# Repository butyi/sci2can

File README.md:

# sci2can

SCI to CAN gateway

## Introduction

This project was developed to receive large data packets from SCI
(RS232 UART without MAX232 line driver) and forward data to CAN
to be available on CAN based tool-chain for analysis purpose.

I decided, this is the perfect moment to get use S08D family, because this
supports faster SCI baud rates than GZ family what I know well.
Therefore I searched my dusty DEMO9S08DZ60 demo board in the deep of cupboard.

## Software

Software is pure assembly code. Funny, it is just 454 bytes long.

### Modules

To understand my description below you may need to look at the related part in
[processor reference manual](https://www.nxp.com/docs/en/data-sheet/MC9S08DZ60.pdf).

#### Central Processor Unit (S08CPUV3)
 
Regarding assembly commands read
[HCS08RMV1.pdf](https://www.nxp.com/docs/en/reference-manual/HCS08RMV1.pdf).
Now (when I am writing this) it is not available on this link even though
I have downloaded from here some weeks before. I have stored it
[here](https://github.com/butyi/sci2can/raw/master/hw/HCS08RMV1.pdf).

My most often read parts are
- Instruction Set Summary (from page 121)
- Branch summary table on sheet of BRA instruction (page 232)

#### Parallel Input/Output Control

To prevent extra current consumption caused by flying not connected input ports,
all ports shall be configured as output. I have configured ports to low level
output by default.
There are only some exceptions for the used ports, where this default
initialization is not proper. For example inputs pins.
This default initialization is proper for FET and OSCILL_SUPP pins, so there is
no specific code for these pins.

#### Multi-purpose Clock Generator (S08MCGV1)

MCG is configured to PEE mode. But this mode can be reached through other modes.
See details in
[AN3499](https://www.nxp.com/docs/en/application-note/AN3499.pdf).
Bus frequency is only 8MHz now, while theoretical maximum is 20MHz.
So here there is improvement potential if software execution is not enough fast.

I have measured bus clock by this code.

Really 8 Mhz, because 8 MHz is 125ns, 10 cycle is 1250ns, which can be seen between edges.

#### Serial Communications Interface (S08SCIV4)

SCI clock is driven by Bus Clock. Maximal baud rate is Bus Clock divided by 16.
Since my Bus Clock is 8MHz, maximum baud rate is 500k baud. Now I just need
baud 125k in this application. It is enough to enable only RX direction.
Data is coming in burst, many bytes immediately after each other. There is
idle period between data bursts.
I use Rx and Idle interrupts. Rx interrupt stores received byte in RAM buffer.
Idle interrupt is invoked when there is one byte long idle state on the serial
line after active period. I use this event to recognize end of data packet
reception. At this moment CAN transmission can be initiated (if packet looks
good) and prepare SCI to next packet.

#### Freescale Controller Area Network (S08MSCANV1)

Regarding CAN clock it is proposed to use external clock directly. With 4MHz
crystal maximum baud rate is 500k baud. This is enough for my needs.
CAN bit consists of 8 time quanta. Sample point is 75% (6+2 tq).
Only transmission is used. Receive related registers are not initialized.
But Tx interrupt is used. Message preparation is done by interrupt routine.
Transmission is triggered by enable Tx interrupt. Then interrupt will send
all CAN messages one after another. Last message disables the interrupt to
stop the transmission of data burst.
Automatic BufOff recovery is configured, there is no other error handling. 
After CAN module initialization, an info message is sent to CAN. This contains
software identification information, like application identifier, software
revision, build date.

### Main loop

#### Structure

Software does not have any operation system. It is not needed, especially
because there no task in main loop. Everything is executed in interrupt
routines.

#### Initialization

Stack, ports, needed modules are initialized one by one.

#### Main activity

The following procedure is executed cyclically.
First SCI Rx interrupt fills up the RAM buffer with data.
After Idle interrupt is called. If amount of received data is proper,
CAN transmission is initialized by enable CAN Tx interrupt.
Then CAN Tx interrupts will send out all data from RAM buffer to CAN.
Last CAN message disables itself (CAN Tx interrupt).
Additional features of hardware is not handled by software yet.

#### Status LED

Meantime RTC interrupt handles the status LED.
The following codes are visible on LED.
- 0001, Short 25% On flash: There is no SCI communication.
- 0011, Medium 50%-50% On-Off flash: Received SCI bytes are not enough.
- 0111, Long 75% On flash: Data cannot be sent to CAN.
- 1111, Always On: Everything are OK, data is forwarded to CAN properly.

#### CAN message structure

The 96 data bytes are transmitted in 12 messages. The CAN ID is the position of
first byte of message in the SCI buffer multiplied by 8. This means
- ID of first message is zero
- ID of second message is 8*8 = 64 dec = 40hex
- ID of third message is 16*8 = 128 dec = 80hex
- ... and so on.

#### Debug support

If OSCILL_SUPP is enabled by compiler switch, execution timing of software
parts can be watched on not used uC pins by oscilloscope.
Here are oscilloscope screenshots about software activity.

- Blue is SCI line. Bursts are visible.

- Blue is SCI Bursts. Red is PTE0 pin, where rising edge is first Rx interrupt
after the idle period, faling edge is idle interrupt.

- Blue is SCI Bursts. Red is PTE1 pin, where rising edge is CAN Tx interrupt
enable, faling edge is end of last CAN Tx interrupt.

- Blue is SCI Bursts. Red is PTE4 pin, high during SCI Rx interrupt execution.

- Blue is SCI Bursts. Red is PTE5 pin, high during CAN Tx interrupt execution.

- Blue is PTE3 pin, high during RTC periodic timer interrupt execution.

- Blue is PTE3 pin, length of RTC periodic timer interrupt execution.

- Blue is PTE4 pin, length of SCI Rx interrupt execution.

- Blue is PTE5 pin, length of CAN Tx interrupt execution.

- Blue is SCI Rx bursts, red is CAN Tx burst.

- Blue is SCI Rx burst, red is SCI Rx interrupt execution.

### Compile

- Download assembler from [aspisys.com](http://www.aspisys.com/asm8.htm).
  It works on both Linux and Windows.
- Check out the repo
- Run my bash file `./c`.
  Or run `asm8 prg.asm` on Linux, `asm8.exe prg.asm` on Windows.
- prg.s19 is now ready to download.

### Download

I have already written [downloader/bootloader for DZ family](https://github.com/butyi/dzbl/).

- First download the bootloader (dzbl/prg.s19) by [USBDM](https://sourceforge.net/projects/usbdm/)
- Create CAN or SCI connection between MCU and PC
- Copy `dzdl.py` to `~/bin/` folder and add executable attribute by `chmox +x ~/bin/dzdl.py`. This is only needed once.
- Run bash file `./p`.

## Hardware

After successful operation of software on demo board I decided to design a
specific PCB.

### Requirements

- At least the following connector pins are needed for gateway function:
  - Ground
  - Power supply ( +7V ... +38V )
  - Serial data input line
  - CAN Low
  - CAN High
- Supply power input must support both 12V and 24V systems.
- Supply power reverse polarity protection needed.
- Small power supply dissipation.
- SCI does not need MAX232 driver because there isn't in the transmitter too.
- SCI port must be protected against connect to supply (+38V).
- CAN transceiver is needed.
- CAN Built in terminator resistor is needed.
- Status LED needed with software control.
- Standard BDM port for software download.
- Small board with direct wire connection (not specific connector).

### Microcontroller

I have used MC9S08DZ60. It is enough for such a small project like this.
Assembler, downloader for both Linux and Windows are available for free for this
family. It costs around 1€.
This is my first application with DZ family controller. After finish the
project, and I have to say, I like it! :) It is really better than GZ family.

Refer to
[processor reference manual](https://www.nxp.com/docs/en/data-sheet/MC9S08DZ60.pdf).

### Clock

External Crystal is used for better CAN performances, this is proposed
by uC manufacturer. Passive parts around are also according to datasheet and
similar to development board circuit.
4MHz is enough up to CAN baud rate 500k when external clock is selected.
For 1Mbaud support I selected rather bus clock of bootloader (16MHz), even though external crystal is proposed.
Crystal is now pin type, since via is need anyway, now the pins holes are vias.

### Connector

I used what I have at home. It is two 3 pins screw connector for wires. 

The connector is not necessary to be mounted, wires can be soldered directly
into the holes. It saves some money and height.

### Power supply

Power input starts with Ds1 diode for reverse polarity protection.
Same circuit as 7805 replacement was designed on the main board.
Search "7805 replacement switching regulator" on Internet.
It uses ME3116. 1A output, max input voltage is 40V.
I just recognized, transient suppression diode is needed on the input. 
Without this protection the supply could damaged at 24V due sparks during 
switch on. I have choosen SMAJ33A.
There is electrolit capacitor on input voltage.
There are also some filter capacitors on uC supply. 
Once is very close to the microcontroller.

### BDM port

BDM port is like proposed in datasheet. This matches to USBDM developer
interface which I use. Single pin communication line (BKGD) has external pull
up resistor, even if it is not necessary.
Reset pin has simple external pull up resistor and filter capacitor.
This port is only needded for software update.
The connector contains extra pins. Details are below.

### SCI input

SCI input is connected to RX pin of SCI2 module. There are serial resistors
for protection against its connection to 24V.
Next is Ui1 74HC1G125GW as impedance adapter. This provides much higher impedance
input than uC pin.
There is Di2 BZT52C4V7 transient suppressor diode to save further parts of
circuit against high voltage tranzients. 
Especially because PTE port has no built in clamp diode to supply.

When Ui1 is mounted, Ri3 and Ri4 are not needed.
Ri3 and Ri4 are designed when pin is used for normal digit or analogue input. 

Ui1 provides perfect shape and amplitude signal for uC input pin.
Here is a screenshot about shape of SCI signal on the uC pin (RxD1).

### CAN output

CAN uses PCA82C251 transceiver. Since there will be point-point connection
on this CAN and other side usually does not have terminator resistor,
there is built in CAN line terminator resistor (Rc2) with 100 Ohm.
Why not 120ohm? Good question.
To limit number of different parts, I have tried to use 100ohm, 1k, 10k, 100k,
1M resistors and 10nF, 100nF, 1uF, 10uF capacitors as many places as possible.
I could buy these parts by 1€/5000pcs. To store it, the cheapest solution
is to buy empty creme holder box in the pharmacy. :smile:
Turning back to CAN.
CAN hardware supports high baud rates up to 1MBaud, but does not support CANFD. 

### Status LED

Status LED (D3) is connected to PTD2. Level high on pin will switch on the LED.
LED is controlled by the software.

Status LED and power LED are near to each other on the back of PCB
intentionally. Plastic box have a hole where the LEDs are, and PCB is fixed in
the box by glue gun. This glue is usually enough transparent to be LED light
visible outside while it is still dust resistant.

### Additional features

Board was designed to be usable for other purposes as well, as much as the
board size allows it. Therefore some components and solutions were also
added to hardware. These are not needed for the original function,
but I hope these will be useful for other functions in the future with the same
board. These components are marked by * on the schematic. These are not need to
be mounted for simple gateway function.

#### Inputs

SCI input is also connected to PTA0. It allows to be used as analogue input.
In this case Ri4 was designed to be used as low side of a voltage divider.
If filter is needed, filter capacitor can be soldered on the top of Ri4 or the
zener.
Similar circuit is also available on the other IO pin without pull down resisor.
When IO pins is used as output, input circuit can be used to monitor the output.

#### Outputs

Hardware has two low side FET outputs. These can switch some external loads,
like lamp, buzzer, relay, or similar.
Gate is pulled down to close FET while port is not yet controlled.
FET was intentionally connected to timer output pins, because this makes outputs
pulse and PWM capable.

OUT ports can also be used as timer input if FET is not mounted but instead a
suitable resistor is mounted between source and gate pins of FET. In this case
this resistor together with gate pull down resistor are a voltage divider.
Filter capacitor (if needed) can be soldered on the top of pull down resistor.
Since FETs are connected to timer ports, this way timer can be used for
pulse length measurement, frequency measurement or similar.

#### Supply measurement

Since there was enough place on PCB and remained several not used ports,
voltage divider was designed from power supply input (UZ) and connected to
PTA5 analogue measurement capable port. With this parts supply voltage can
be measured by the software and used for any purpose.

#### BDM extra pins

The original 6 pins connector contains also SCI1 Rx and Tx pins.
This is designed to be used for software update and debug terminal.

I have extended the debugger connector by 4 additional pins. These are now
the IIC/SPI pins as preparation to connect some IIC or SPI display to board.
I use it now for a small 0.96 col OLED IIC display.

### Printed Circuit Board

#### Design

PCB was designed on [KiCad](https://kicad-pcb.org/), which is a free
PCB development environment on works also on Linux.
It works well, I really like to use it. I was so satisfied, I have donated the
project through [Linux Foundation.](https://www.linuxfoundation.org/).
I have exported schematic in PDF for those who do not have KiCad installed.
[Here is schematic](https://github.com/butyi/sci2can/raw/master/hw/sci2can_sch.pdf).

Designed PCB is a small board with size 30x30 mm to fit into mentioned box.
Here are some pictures about the board design in KiCad.

#### Production

A-sample PCBs (V1.00) were produced by [SOS PCB Kft.](https://nyakexpressz.hu/).
I was satisfied with quality of production. 

I have ordered second generation PCB from China with SMD mounting.
Result is sufficient.

### Mounting

R and C components on the bottom side were mounted by PCB producer.
I have to mount only the up side components by hand.

Note, take care to low resistance of solder paste. Use as less as possible,
and always remove remainings by water.

### Box

Here are pictures about V1.00 prototype.

I have ordered this box for null-series:

Simple, cheap, small. Perfect.

Here are pictures about V1.02. This series has a 0.96 inch OLED 128x64 pixels
display and two capacitive touch buttons. Suppressor diodes are still mounted
into IO ports, because these were not yet designed on the board.

### Costs

- PCB: 3€
- Microcontroller: 2€ (due to I have bought small amount)
- CAN transceiver: 0.25€
- Switching power supply board: 2€
- Screw connector: 0.5€
- Passive components (all together): 1€
- Box: 1€

Most of them are from [ebay](https://www.ebay.com/).
All together 10€ a product without human costs (development, assembly) and
without profit.

## Workshop

Finally here is a picture about my workshop corner. :smile:

Left side there is russian microscope, right is also russian soldering iron.

## License

This is free. You can do anything you want with it.
While I am using Linux, I got so many support from free projects,
I am happy if I can give something back to the community.

## Notes

I have used `mogrify -resize 640x640\> *` command to downsize the images.
Here `\>` means only shrink larger images and do not enlarge.

## Keywords

Motorola, Freescale, NXP, MC68HC9S08DZ60, 68HC9S08DZ60, HC9S08DZ60, MC9S08DZ60,
9S08DZ60, HC9S08DZ48, HC9S08DZ32, HC9S08DZ, 9S08DZ, UART, RS232.

###### 2020 Janos BENCSIK

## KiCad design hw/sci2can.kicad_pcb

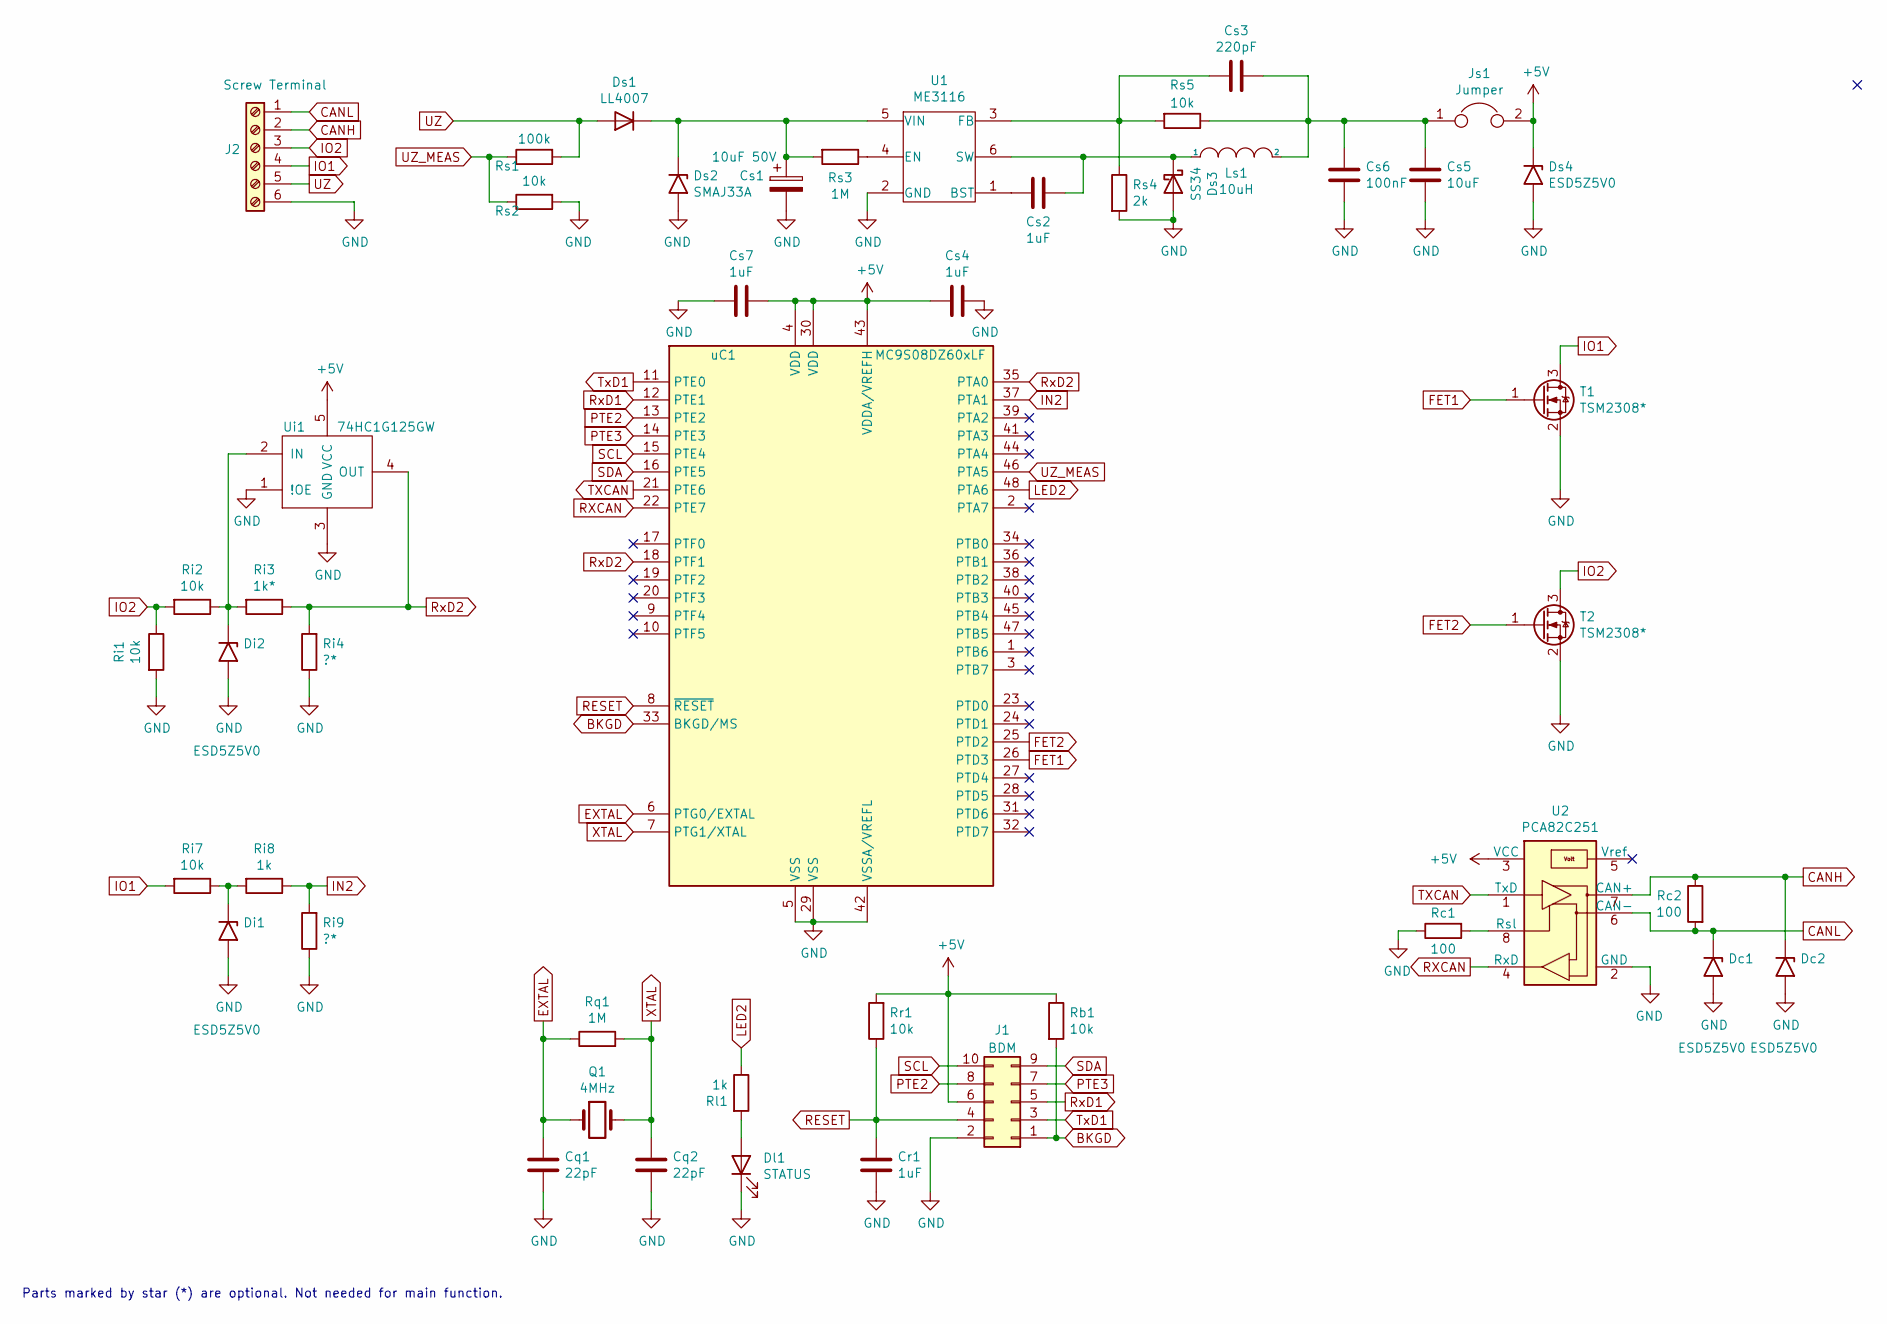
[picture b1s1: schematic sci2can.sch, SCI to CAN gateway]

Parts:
Cq1, Cq2: 22pF; C_0603_1608Metric_Pad1.05x0.95mm_HandSolder
Cr1: 1uF; C_0603_1608Metric_Pad1.05x0.95mm_HandSolder
Cs1: 10uF 50V; C_Elec_5x5.8
Cs2, Cs4, Cs7: 1uF; C_0603_1608Metric_Pad1.05x0.95mm_HandSolder
Cs3: 220pF; C_0603_1608Metric_Pad1.05x0.95mm_HandSolder
Cs5: 10uF; C_0603_1608Metric_Pad1.05x0.95mm_HandSolder
Cs6: 100nF; C_0603_1608Metric_Pad1.05x0.95mm_HandSolder
Dc1, Dc2: ESD5Z5V0; D_SOD-523
Di1, Di2: ESD5Z5V0; D_SOD-523
Dl1: STATUS; D_0603_1608Metric_Pad1.05x0.95mm_HandSolder
Ds1: LL4007; D_SMB
Ds2: SMAJ33A; D_SMA
Ds3: SS34; D_SMA
Ds4: ESD5Z5V0; D_SOD-523
J1: BDM; PinHeader_2x05_P2.54mm_Vertical
J2: Screw Terminal; TerminalBlock_Phoenix_MKDS-1,5-6_1x06_P5.00mm_Horizontal
Js1: Jumper; SolderJumper-2_P1.3mm_Open_RoundedPad1.0x1.5mm
Ls1: 10uH; L_2816_7142Metric_Pad3.20x4.45mm_HandSolder
Q1: 4MHz; Crystal_HC49-4H_Vertical
Rb1: 10k; R_0603_1608Metric_Pad1.05x0.95mm_HandSolder
Rc1, Rc2: 100; R_0603_1608Metric_Pad1.05x0.95mm_HandSolder
Ri1, Ri2, Ri7: 10k; R_0603_1608Metric_Pad1.05x0.95mm_HandSolder
Ri3: 1k*; R_0603_1608Metric_Pad1.05x0.95mm_HandSolder
Ri4, Ri9: ?*; R_0603_1608Metric_Pad1.05x0.95mm_HandSolder
Ri8: 1k; R_0603_1608Metric_Pad1.05x0.95mm_HandSolder
Rl1: 1k; R_0603_1608Metric_Pad1.05x0.95mm_HandSolder
Rq1: 1M; R_0603_1608Metric_Pad1.05x0.95mm_HandSolder
Rr1: 10k; R_0603_1608Metric_Pad1.05x0.95mm_HandSolder
Rs1: 100k; R_0603_1608Metric_Pad1.05x0.95mm_HandSolder
Rs2, Rs5: 10k; R_0603_1608Metric_Pad1.05x0.95mm_HandSolder
Rs3: 1M; R_0603_1608Metric_Pad1.05x0.95mm_HandSolder
Rs4: 2k; R_0603_1608Metric_Pad1.05x0.95mm_HandSolder
T1, T2: TSM2308*; SOT-23
U1: ME3116; SOT-23-6_Handsoldering
U2: PCA82C251; SOIC-8_3.9x4.9mm_P1.27mm
Ui1: 74HC1G125GW; SOT-353_SC-70-5_Handsoldering
uC1: MC9S08DZ60xLF; LQFP-48_7x7mm_P0.5mm

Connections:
+5V: Cs4.1, Cs7.2, Ds4.1 (A1), J1.6, Js1.2, Rb1.1, Rr1.2, U2.3 (VCC), Ui1.5 (VCC), uC1.4 (VDD), uC1.30 (VDD), uC1.43 (VDDA/VREFH)
BKGD: J1.1, Rb1.2, uC1.33 (BKGD/MS)
CANH: Dc2.1 (A1), J2.2, Rc2.1, U2.7 (CAN+)
CANL: Dc1.1 (A1), J2.1, Rc2.2, U2.6 (CAN-)
EXTAL: Cq1.1, Q1.1, Rq1.1, uC1.6 (PTG0/EXTAL)
FET1: T1.1 (G), uC1.26 (PTD3)
FET2: T2.1 (G), uC1.25 (PTD2)
GND: Cq1.2, Cq2.2, Cr1.2, Cs1.2, Cs4.2, Cs5.2, Cs6.2, Cs7.1, Dc1.2 (A2), Dc2.2 (A2), Di1.2 (A2), Di2.2 (A2), Dl1.1 (K), Ds2.2 (A2), Ds3.2 (A), Ds4.2 (A2), J1.2, J2.6, Rc1.1, Ri1.2, Ri4.1, Ri9.1, Rs2.2, Rs4.2, T1.2 (S), T2.2 (S), U1.2 (GND), U2.2 (GND), Ui1.1 (!OE), Ui1.3 (GND), uC1.5 (VSS), uC1.29 (VSS), uC1.42 (VSSA/VREFL)
IN2: Ri8.1, Ri9.2, uC1.37 (PTA1)
IO1: J2.4, Ri7.2, T1.3 (D)
IO2: J2.3, Ri1.1, Ri2.2, T2.3 (D)
LED2: Rl1.1, uC1.48 (PTA6)
unnamed: Cs1.1, Ds1.1 (K), Ds2.1 (A1), Rs3.2, U1.5 (VIN)
unnamed: Cs2.1, U1.1 (BST)
unnamed: Cs2.2, Ds3.1 (K), Ls1.1, U1.6 (SW)
unnamed: Cs3.1, Rs4.1, Rs5.2, U1.3 (FB)
unnamed: Cs3.2, Cs5.1, Cs6.1, Js1.1, Ls1.2, Rs5.1
unnamed: Di1.1 (A1), Ri7.1, Ri8.2
unnamed: Di2.1 (A1), Ri2.1, Ri3.2, Ui1.2 (IN)
unnamed: Dl1.2 (A), Rl1.2
unnamed: Rc1.2, U2.8 (Rsl)
unnamed: Rs3.1, U1.4 (EN)
PTE2: J1.8, uC1.13 (PTE2)
PTE3: J1.7, uC1.14 (PTE3)
RESET: Cr1.1, J1.4, Rr1.1, uC1.8 (~RESET)
RXCAN: U2.4 (RxD), uC1.22 (PTE7)
RxD1: J1.5, uC1.12 (PTE1)
RxD2: Ri3.1, Ri4.2, Ui1.4 (OUT), uC1.18 (PTF1), uC1.35 (PTA0)
SCL: J1.10, uC1.15 (PTE4)
SDA: J1.9, uC1.16 (PTE5)
TXCAN: U2.1 (TxD), uC1.21 (PTE6)
TxD1: J1.3, uC1.11 (PTE0)
UZ: Ds1.2 (A), J2.5, Rs1.2
UZ_MEAS: Rs1.1, Rs2.1, uC1.46 (PTA5)
XTAL: Cq2.1, Q1.2, Rq1.2, uC1.7 (PTG1/XTAL)

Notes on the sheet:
Parts marked by star (*) are optional. Not needed for main function.

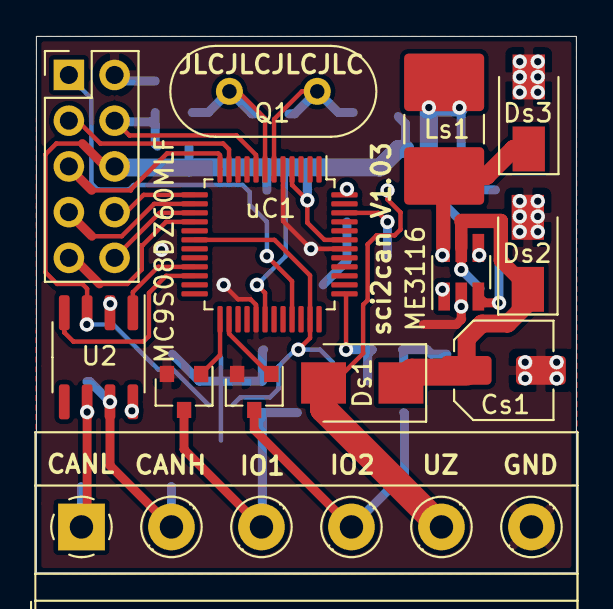
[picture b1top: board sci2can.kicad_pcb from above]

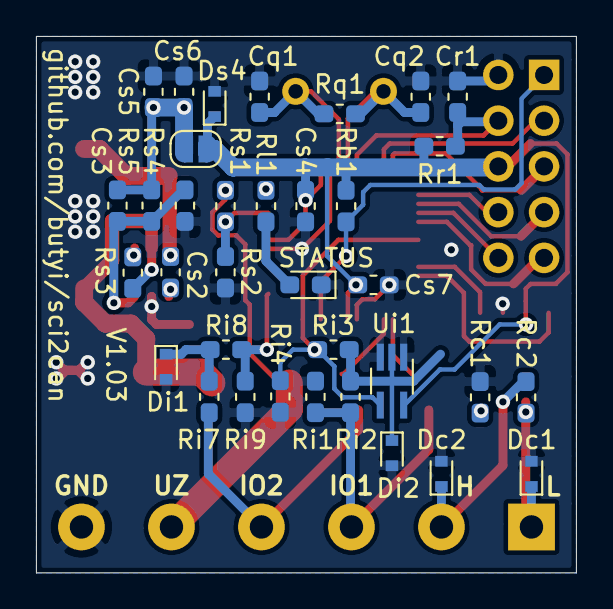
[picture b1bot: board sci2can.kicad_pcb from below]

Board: 2 copper layers, 30.0 x 29.8 mm, 48 parts (35 on the bottom side), 35 nets.

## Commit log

2020-05-08 Create RAEDME file
2020-05-23 Initial revision
2020-05-23 image resize
2020-05-23 readme fix
2020-05-23 readme update
2020-05-24 image crop
2020-05-24 comment fix
2020-05-27 readme fix and gitignore for compiler output files
2020-06-15 sw: COP added
2020-06-20 hw 1v02
2020-08-25 HW SW update, 0.96 inch display
2020-08-25 file cleanup
2021-02-26 Button frozzen voltage update fixed
2021-02-26 trailing spaces removed
2021-02-27 Button pullup enabled
2021-02-28 Buttons active low
2021-02-28 git test, whitespace only
2023-10-28 Update for working with bootloader (dzbl)
2023-10-28 readme update with bootloader
2023-10-28 code comment restored
